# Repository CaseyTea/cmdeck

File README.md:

Watch the build video ↓

CM Deck is a clamshell style cyberdeck built around the Raspberry Pi Compute Module 5. It has a custom carrier board and a low profile mechanical keyboard.

<sub>⚠️ The PCBs will be updated to fix three issues: 1. The flash chip CS pin isn’t connected (see video at [11:09](https://youtu.be/U5GZeMm5nhI?si=vS6aNDHk9gTeop53&t=669)) | 2. Add jumper pads for the power button so I can solder wires and connect it to the power board (see video at [16:32](https://youtu.be/U5GZeMm5nhI?si=_Pz7x-TjfpxkA6fn&t=992)) | 3. Add an open jumper pad on the 3V3 line of the DSI connector on the main board (see video at [15:09](https://youtu.be/U5GZeMm5nhI?si=e3sX7tEprCDsY_S7&t=909))</sub>

[![CC BY-NC-SA 4.0][cc-by-nc-sa-shield]][cc-by-nc-sa]

[![CC BY-NC-SA 4.0][cc-by-nc-sa-image]][cc-by-nc-sa]

[cc-by-nc-sa]: http://creativecommons.org/licenses/by-nc-sa/4.0/
[cc-by-nc-sa-image]: https://licensebuttons.net/l/by-nc-sa/4.0/88x31.png
[cc-by-nc-sa-shield]: https://img.shields.io/badge/License-CC%20BY--NC--SA%204.0-lightgrey.svg

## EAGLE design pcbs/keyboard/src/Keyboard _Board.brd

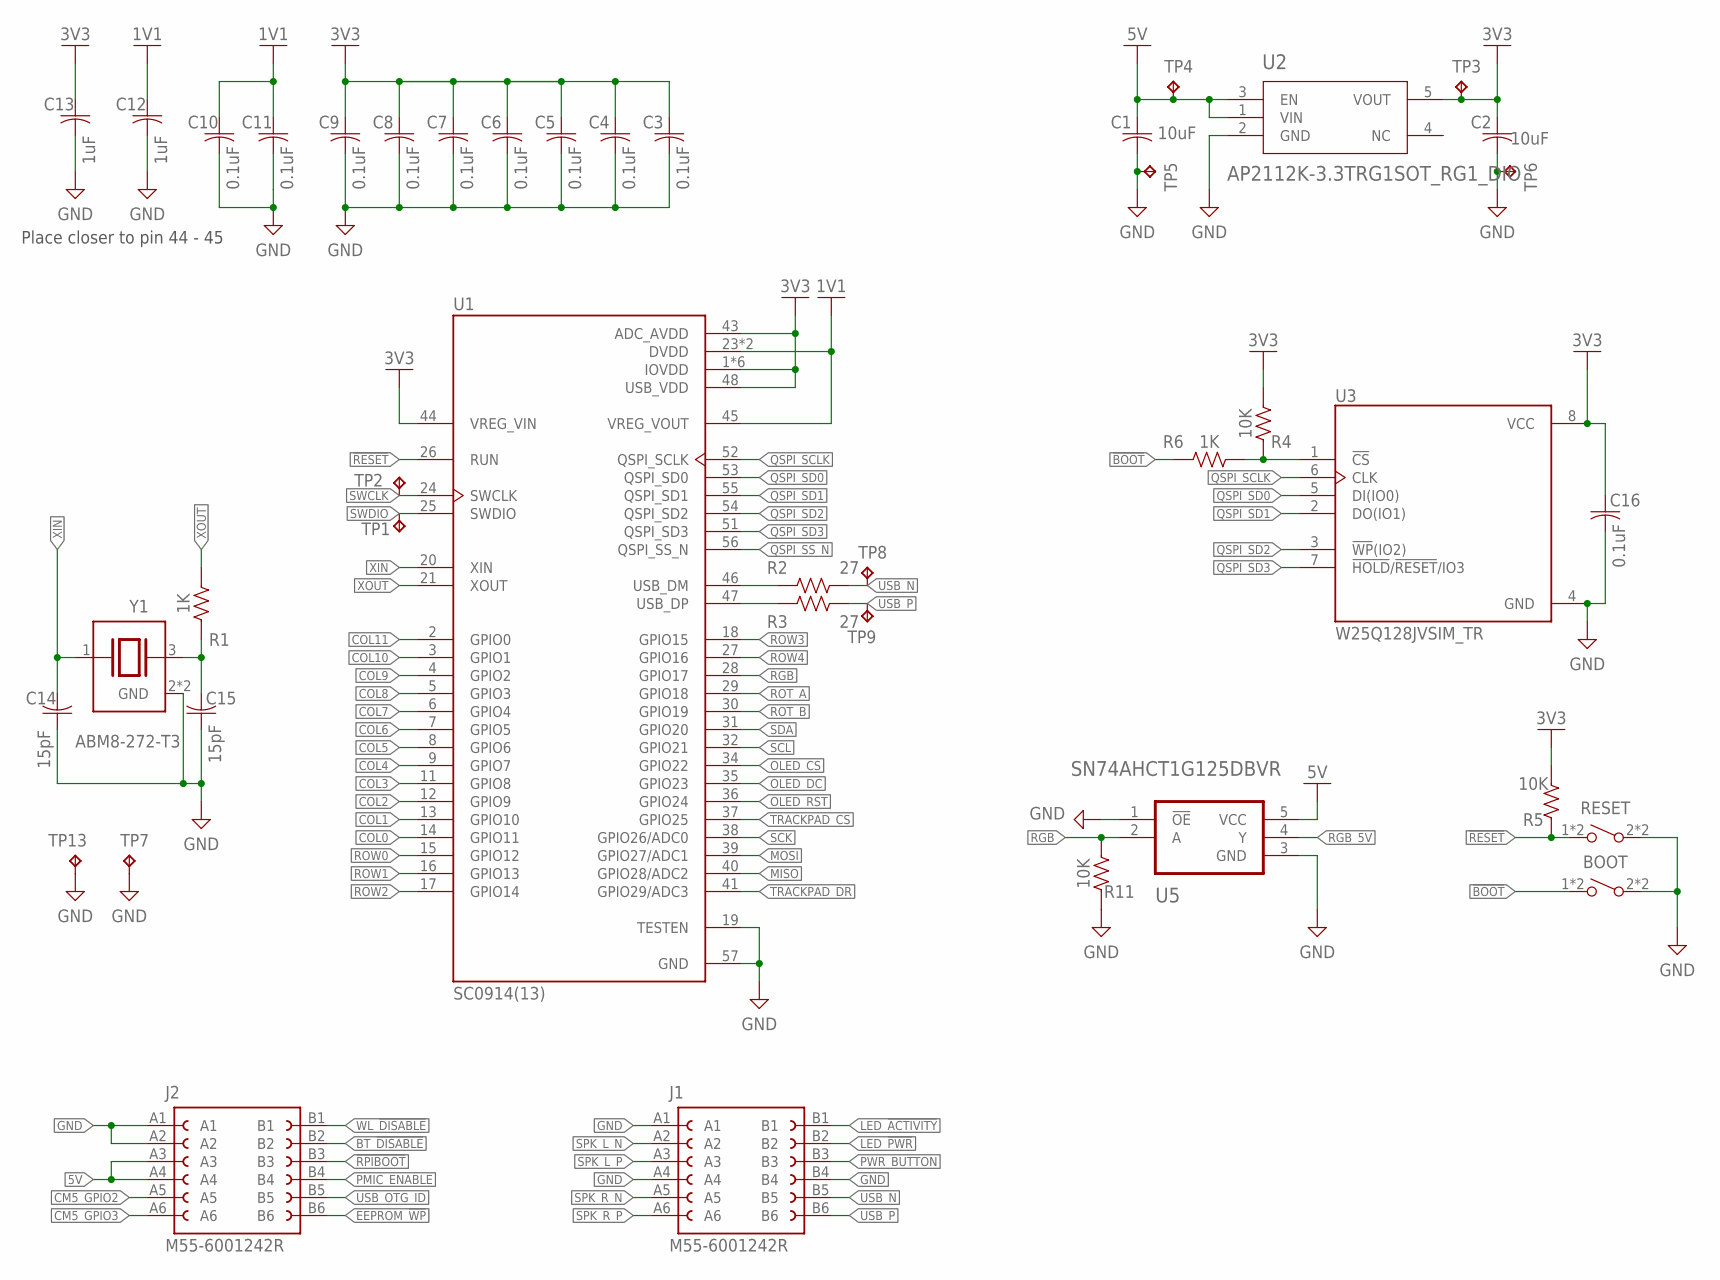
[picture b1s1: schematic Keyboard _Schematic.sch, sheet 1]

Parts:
BOOT: SPST-NO_SWITCH_KMR2; KMR2
C1, C2: 10uF; CAPC3216X135
C3, C4, C5, C6, C7, C8, C9, C10, C11, C16: 0.1uF; CAPC2012X110
C12, C13: 1uF; CAPC2012X110
C14, C15: 15pF; CAPC2012X110
J1, J2: M55-6001242R; HARWIN_M55-6001242R
R1, R6: 1K; RESC2012X65
R2, R3: 27; RESC2012X65
R4, R5, R11: 10K; RESC2012X65
RESET: SPST-NO_SWITCH_KMR2; KMR2
TP1, TP2, TP3, TP5, TP13: TPB2,54; B2,54
TP4, TP6, TP7, TP8, TP9: TPB1,27; B1,27
U1: SC0914(13); QFN40P700X700X90-57N
U2: AP2112K-3.3TRG1SOT_RG1_DIO; SOT_RG1_DIO
U3: W25Q128JVSIM_TR; SOIC127P790X216-8N
U5: SN74AHCT1G125DBVR; SOT95P280X145-5N
Y1: ABM8-272-T3; XTAL_ABM8-272-T3

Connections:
1V1: C10.1, C11.1, C12.1, U1.23 (DVDD), U1.45 (VREG_VOUT), U1.50 (DVDD)
3V3: C2.1, C3.1, C4.1, C5.1, C6.1, C7.1, C8.1, C9.1, C13.1, C16.1, R4.2, R5.2, TP3.TP, U1.1 (IOVDD), U1.10 (IOVDD), U1.22 (IOVDD), U1.33 (IOVDD), U1.42 (IOVDD), U1.43 (ADC_AVDD), U1.44 (VREG_VIN), U1.48 (USB_VDD), U1.49 (IOVDD), U2.5 (VOUT), U3.8 (VCC); also elsewhere on the board
5V: C1.1, J2.A3, J2.A4, TP4.TP, U2.1 (VIN), U2.3 (EN), U5.5 (VCC); also elsewhere on the board
!BOOT: BOOT.1, BOOT.4 (1), R6.1
!RESET: R5.1, RESET.1, RESET.4 (1), U1.26 (RUN)
!RPIBOOT: J2.B3; also elsewhere on the board
BT_!DISABLE: J2.B2; also elsewhere on the board
CM5_GPIO2: J2.A5; also elsewhere on the board
CM5_GPIO3: J2.A6; also elsewhere on the board
COL0: U1.14 (GPIO11); also elsewhere on the board
COL1: U1.13 (GPIO10); also elsewhere on the board
COL2: U1.12 (GPIO9); also elsewhere on the board
COL3: U1.11 (GPIO8); also elsewhere on the board
COL4: U1.9 (GPIO7); also elsewhere on the board
COL5: U1.8 (GPIO6); also elsewhere on the board
COL6: U1.7 (GPIO5); also elsewhere on the board
COL7: U1.6 (GPIO4); also elsewhere on the board
COL8: U1.5 (GPIO3); also elsewhere on the board
COL9: U1.4 (GPIO2); also elsewhere on the board
COL10: U1.3 (GPIO1); also elsewhere on the board
COL11: U1.2 (GPIO0); also elsewhere on the board
EEPROM_!WP: J2.B6; also elsewhere on the board
GND: BOOT.2, BOOT.3 (2), C1.2, C2.2, C3.2, C4.2, C5.2, C6.2, C7.2, C8.2, C9.2, C10.2, C11.2, C12.2, C13.2, C14.1, C15.1, C16.2, J1.A1, J1.A4, J1.B4, J2.A1, J2.A2, R11.1, RESET.2, RESET.3 (2), TP5.TP, TP6.TP, TP7.TP, TP13.TP, U1.19 (TESTEN), U1.57 (GND), U2.2 (GND), U3.4 (GND), U5.1 (!OE), U5.3 (GND), Y1.2 (GND), Y1.4 (GND); also elsewhere on the board
LED_!ACTIVITY: J1.B1; also elsewhere on the board
LED_!PWR: J1.B2; also elsewhere on the board
MISO: U1.40 (GPIO28/ADC2); also elsewhere on the board
MOSI: U1.39 (GPIO27/ADC1); also elsewhere on the board
unnamed: C15.2, R1.1, Y1.3
OLED_CS: U1.34 (GPIO22); also elsewhere on the board
OLED_DC: U1.35 (GPIO23); also elsewhere on the board
OLED_RST: U1.36 (GPIO24); also elsewhere on the board
PMIC_ENABLE: J2.B4; also elsewhere on the board
PWR_BUTTON: J1.B3; also elsewhere on the board
QSPI_SCLK: U1.52 (QSPI_SCLK), U3.6 (CLK)
QSPI_SD0: U1.53 (QSPI_SD0), U3.5 (DI(IO0))
QSPI_SD1: U1.55 (QSPI_SD1), U3.2 (DO(IO1))
QSPI_SD2: U1.54 (QSPI_SD2), U3.3 (!WP!(IO2))
QSPI_SD3: U1.51 (QSPI_SD3), U3.7 (!HOLD!/!RESET!/IO3)
QSPI_SS_N: R4.1, R6.2, U1.56 (QSPI_SS_N), U3.1 (!CS)
RGB: R11.2, U1.28 (GPIO17), U5.2 (A)
RGB_5V: U5.4 (Y); also elsewhere on the board
ROT_A: U1.29 (GPIO18); also elsewhere on the board
ROT_B: U1.30 (GPIO19); also elsewhere on the board
ROW0: U1.15 (GPIO12); also elsewhere on the board
ROW1: U1.16 (GPIO13); also elsewhere on the board
ROW2: U1.17 (GPIO14); also elsewhere on the board
ROW3: U1.18 (GPIO15); also elsewhere on the board
ROW4: U1.27 (GPIO16); also elsewhere on the board
SCK: U1.38 (GPIO26/ADC0); also elsewhere on the board
SCL: U1.32 (GPIO21); also elsewhere on the board
SDA: U1.31 (GPIO20); also elsewhere on the board
SPK_L_N: J1.A2; also elsewhere on the board
SPK_L_P: J1.A3; also elsewhere on the board
SPK_R_N: J1.A5; also elsewhere on the board
SPK_R_P: J1.A6; also elsewhere on the board
SWCLK: TP2.TP, U1.24 (SWCLK)
SWDIO: TP1.TP, U1.25 (SWDIO)
TRACKPAD_CS: U1.37 (GPIO25); also elsewhere on the board
TRACKPAD_DR: U1.41 (GPIO29/ADC3); also elsewhere on the board
USB_D_N: R2.1, U1.46 (USB_DM)
USB_D_P: R3.2, U1.47 (USB_DP)
USB_N: J1.B5, R2.2, TP8.TP
USB_OTG_ID: J2.B5; also elsewhere on the board
USB_P: J1.B6, R3.1, TP9.TP
WL_!DISABLE: J2.B1; also elsewhere on the board
XIN: C14.2, U1.20 (XIN), Y1.1
XOUT: R1.2, U1.21 (XOUT)

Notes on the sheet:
Place closer to pin 44 - 45

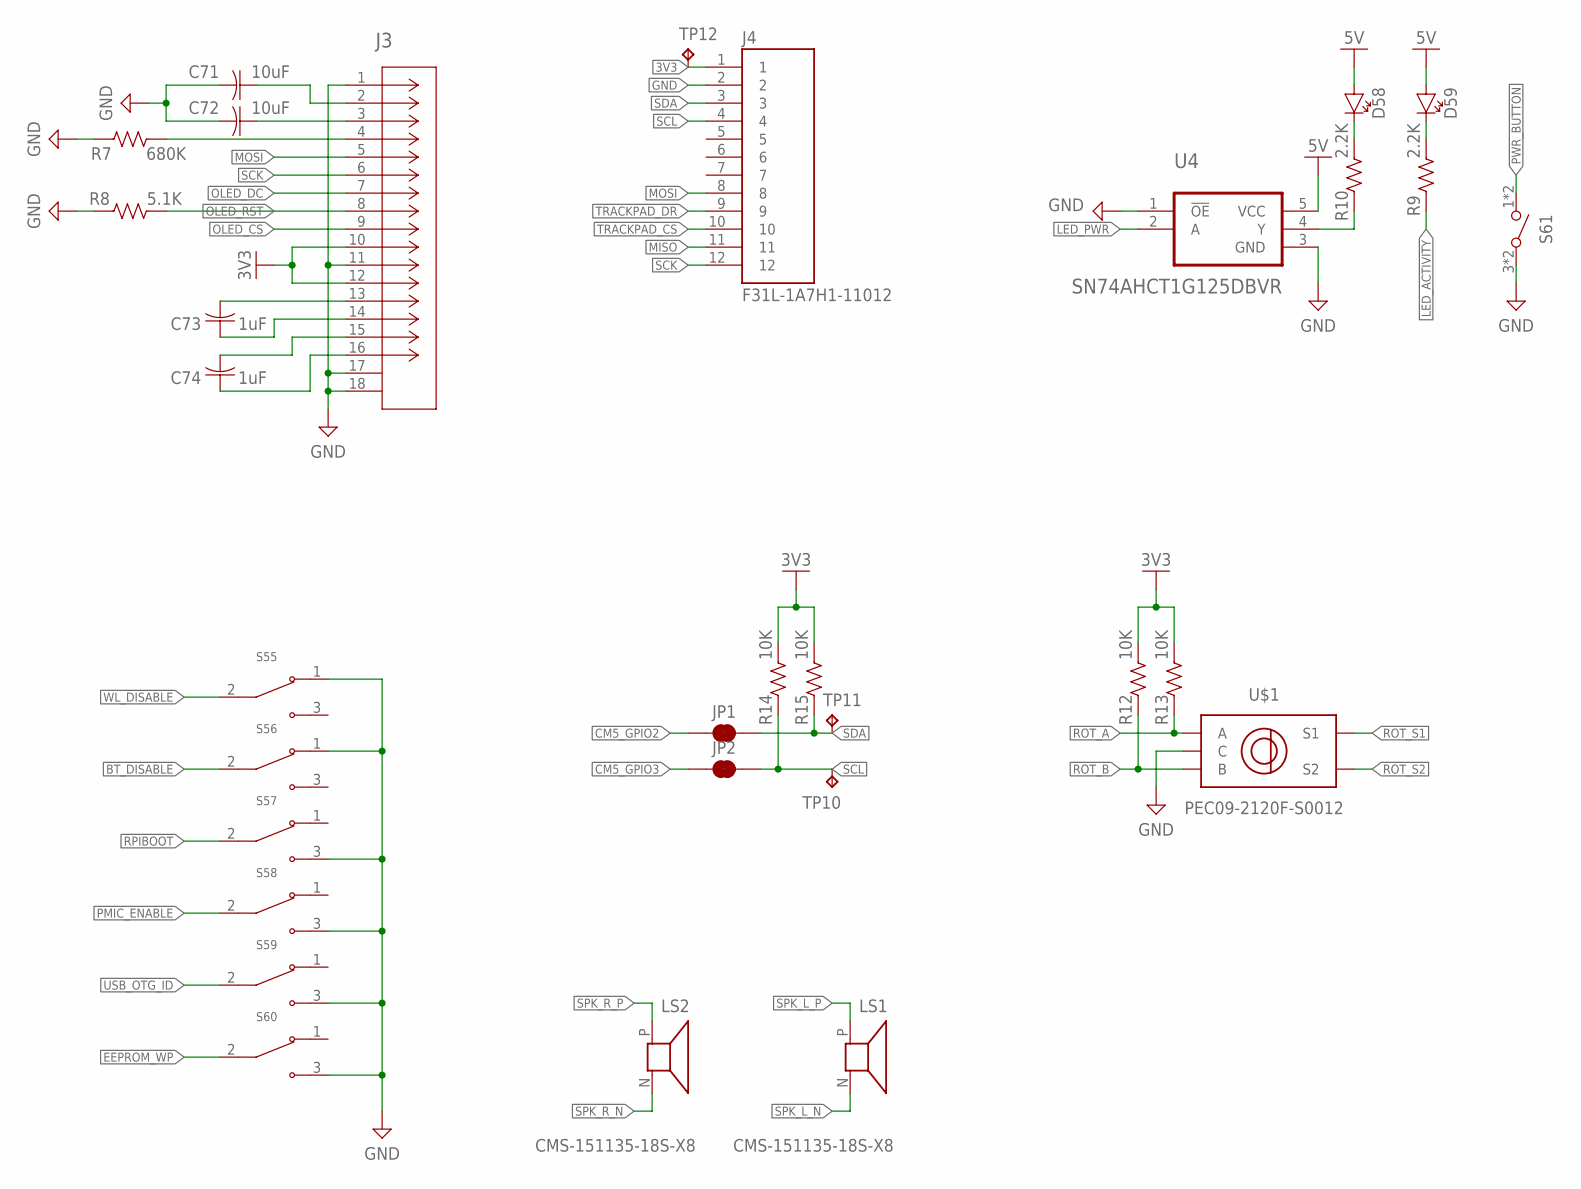
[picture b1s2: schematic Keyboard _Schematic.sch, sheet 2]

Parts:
C71, C72: 10uF; CAPC3216X135
C73, C74: 1uF; CAPC2012X110
D58, D59: CHIP-FLAT-G_1206; LEDC3216X75N_FLAT-G
J3: 1-1775333-6CONN16_1-1775333-6_TEC; CONN16_1-1775333-6_TEC
J4: F31L-1A7H1-11012; AMPHENOL_F31L-1A7H1-11012
JP1, JP2: JUMPER-SMT_2_NC_TRACE_NO-SILK; SMT-JUMPER_2_NC_TRACE_NO-SILK
LS1, LS2: CMS-151135-18S-X8; SPKR_CMS-151135-18S-X8
R7: 680K; RESC2012X65
R8: 5.1K; RESC2012X65
R9, R10: 2.2K; RESC2012X65
R12, R13, R14, R15: 10K; RESC2012X65
S55, S56, S57, S58, S59, S60: SLW-1277744-3A-N-D; SW_SLW-1277744-3A-N-D
S61: SPST-NO_SWITCH_PTS645-SMT-6MM; PTS645-SMT-6MM
TP10, TP11, TP12: TPB1,27; B1,27
U4: SN74AHCT1G125DBVR; SOT95P280X145-5N
U$1: PEC09-2120F-S0012; PEC09-2XXXF-SXXXX

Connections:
3V3: J3.10, J3.12, J4.1, R12.2, R13.2, R14.2, R15.2, TP12.TP; also elsewhere on the board
5V: D58.A, D59.A, U4.5 (VCC); also elsewhere on the board
!RPIBOOT: S57.2; also elsewhere on the board
BT_!DISABLE: S56.2; also elsewhere on the board
CM5_GPIO2: JP1.1; also elsewhere on the board
CM5_GPIO3: JP2.1; also elsewhere on the board
EEPROM_!WP: S60.2; also elsewhere on the board
GND: C71.2, C72.2, J3.1, J3.11, J3.17, J3.18, J4.2, R7.1, R8.1, S55.1, S56.1, S57.3, S58.3, S59.3, S60.3, S61.3 (2), S61.4 (2), U4.1 (!OE), U4.3 (GND), U$1.P$2 (C); also elsewhere on the board
LED_!ACTIVITY: R9.1; also elsewhere on the board
LED_!PWR: U4.2 (A); also elsewhere on the board
MISO: J4.11; also elsewhere on the board
MOSI: J3.5, J4.8; also elsewhere on the board
unnamed: D59.C, R9.2
unnamed: C71.1, J3.2
unnamed: C72.1, J3.3
unnamed: J3.4, R7.2
unnamed: C73.2, J3.13
unnamed: C73.1, J3.14
unnamed: C74.2, J3.15
unnamed: C74.1, J3.16
unnamed: D58.C, R10.2
unnamed: R10.1, U4.4 (Y)
OLED_CS: J3.9; also elsewhere on the board
OLED_DC: J3.7; also elsewhere on the board
OLED_RST: J3.8, R8.2; also elsewhere on the board
PMIC_ENABLE: S58.2; also elsewhere on the board
PWR_BUTTON: S61.1, S61.2 (1); also elsewhere on the board
ROT_A: R13.1, U$1.P$3 (A); also elsewhere on the board
ROT_B: R12.1, U$1.P$1 (B); also elsewhere on the board
ROT_S1: U$1.P$4 (S1); also elsewhere on the board
ROT_S2: U$1.P$5 (S2); also elsewhere on the board
SCK: J3.6, J4.12; also elsewhere on the board
SCL: J4.4, JP2.2, R14.1, TP10.TP; also elsewhere on the board
SDA: J4.3, JP1.2, R15.1, TP11.TP; also elsewhere on the board
SPK_L_N: LS1.N; also elsewhere on the board
SPK_L_P: LS1.P; also elsewhere on the board
SPK_R_N: LS2.N; also elsewhere on the board
SPK_R_P: LS2.P; also elsewhere on the board
TRACKPAD_CS: J4.10; also elsewhere on the board
TRACKPAD_DR: J4.9; also elsewhere on the board
USB_OTG_ID: S59.2; also elsewhere on the board
WL_!DISABLE: S55.2; also elsewhere on the board

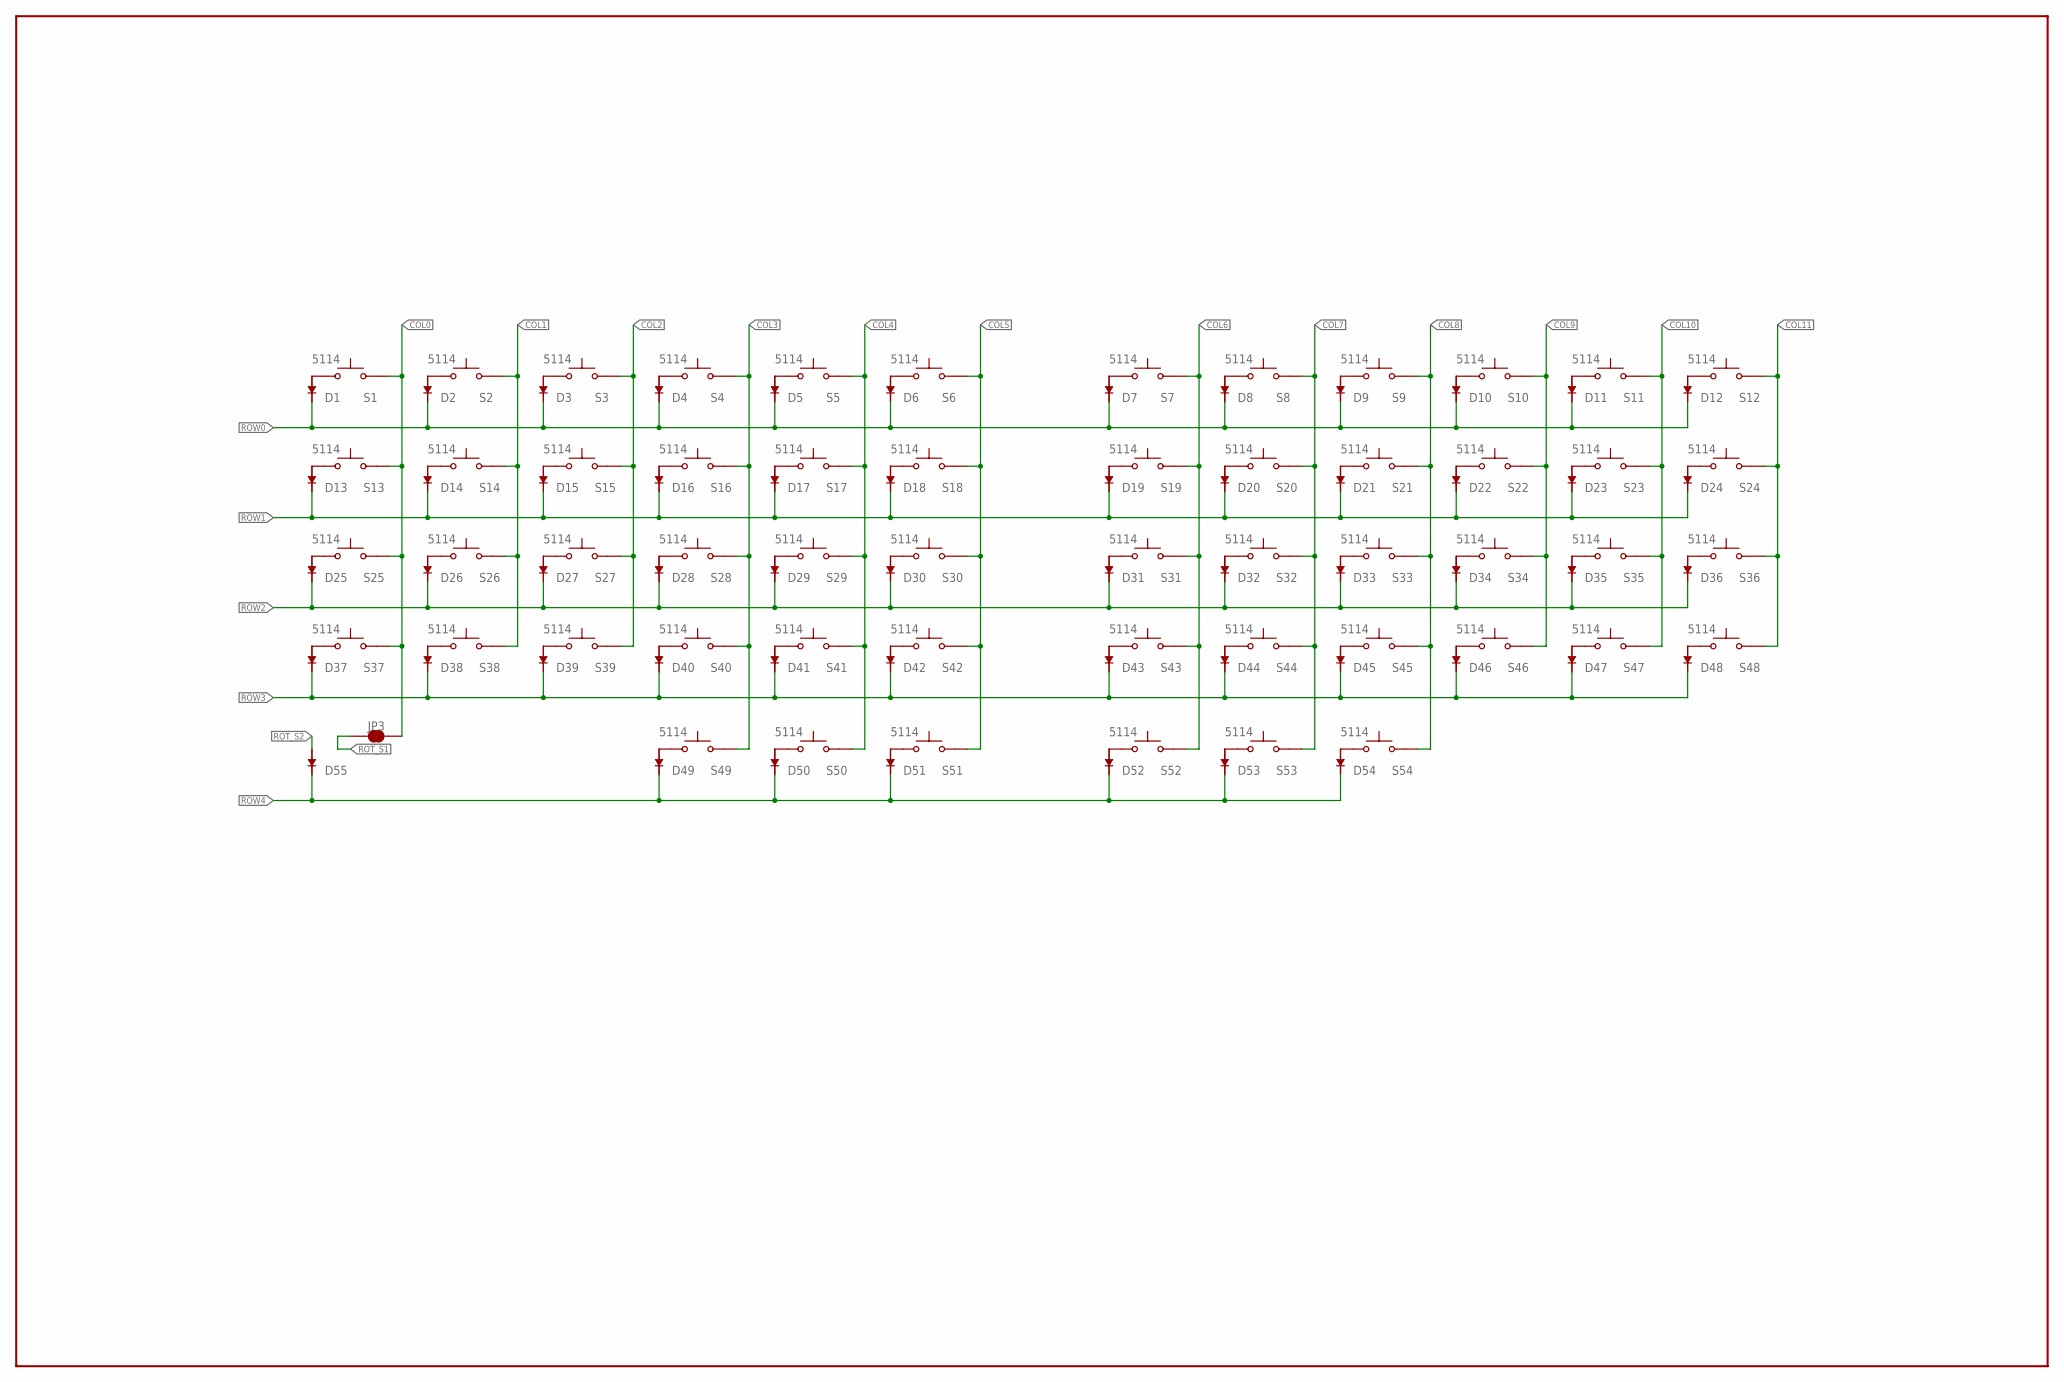
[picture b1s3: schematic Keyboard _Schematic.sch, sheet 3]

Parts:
D1, D2, D3, D4, D5, D6, D7, D8, D9, D10, D11, D12, D13, D14, D15, D16, D17, D18, D19, D20, D21, D22, D23, D24, D25, D26, D27, D28, D29, D30, D31, D32, D33, D34, D35, D36, D37, D38, D39, D40, D41, D42, D43, D44, D45, D46, D47, D48, D49, D50, D51, D52, D53, D54, D55: 1N4148W; SOD3715X135N
JP3: JUMPER-SMT_2_NC_TRACE_NO-SILK; SMT-JUMPER_2_NC_TRACE_NO-SILK
S1, S2, S3, S4, S5, S6, S7, S8, S9, S10, S11, S12, S13, S14, S15, S16, S17, S18, S19, S20, S21, S22, S23, S24, S25, S26, S27, S28, S29, S30, S31, S32, S33, S34, S35, S36, S37, S38, S39, S40, S41, S42, S43, S44, S45, S46, S47, S48, S49, S50, S51, S52, S53, S54: 5114; SW_5114

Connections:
COL0: JP3.1, S1.P$2 (2), S13.P$2 (2), S25.P$2 (2), S37.P$2 (2); also elsewhere on the board
COL1: S2.P$2 (2), S14.P$2 (2), S26.P$2 (2), S38.P$2 (2); also elsewhere on the board
COL2: S3.P$2 (2), S15.P$2 (2), S27.P$2 (2), S39.P$2 (2); also elsewhere on the board
COL3: S4.P$2 (2), S16.P$2 (2), S28.P$2 (2), S40.P$2 (2), S49.P$2 (2); also elsewhere on the board
COL4: S5.P$2 (2), S17.P$2 (2), S29.P$2 (2), S41.P$2 (2), S50.P$2 (2); also elsewhere on the board
COL5: S6.P$2 (2), S18.P$2 (2), S30.P$2 (2), S42.P$2 (2), S51.P$2 (2); also elsewhere on the board
COL6: S7.P$2 (2), S19.P$2 (2), S31.P$2 (2), S43.P$2 (2), S52.P$2 (2); also elsewhere on the board
COL7: S8.P$2 (2), S20.P$2 (2), S32.P$2 (2), S44.P$2 (2), S53.P$2 (2); also elsewhere on the board
COL8: S9.P$2 (2), S21.P$2 (2), S33.P$2 (2), S45.P$2 (2), S54.P$2 (2); also elsewhere on the board
COL9: S10.P$2 (2), S22.P$2 (2), S34.P$2 (2), S46.P$2 (2); also elsewhere on the board
COL10: S11.P$2 (2), S23.P$2 (2), S35.P$2 (2), S47.P$2 (2); also elsewhere on the board
COL11: S12.P$2 (2), S24.P$2 (2), S36.P$2 (2), S48.P$2 (2); also elsewhere on the board
unnamed: D1.A, S1.P$1 (1)
unnamed: D2.A, S2.P$1 (1)
unnamed: D3.A, S3.P$1 (1)
unnamed: D4.A, S4.P$1 (1)
unnamed: D5.A, S5.P$1 (1)
unnamed: D6.A, S6.P$1 (1)
unnamed: D7.A, S7.P$1 (1)
unnamed: D8.A, S8.P$1 (1)
unnamed: D9.A, S9.P$1 (1)
unnamed: D10.A, S10.P$1 (1)
unnamed: D11.A, S11.P$1 (1)
unnamed: D12.A, S12.P$1 (1)
unnamed: D13.A, S13.P$1 (1)
unnamed: D14.A, S14.P$1 (1)
unnamed: D15.A, S15.P$1 (1)
unnamed: D16.A, S16.P$1 (1)
unnamed: D17.A, S17.P$1 (1)
unnamed: D18.A, S18.P$1 (1)
unnamed: D19.A, S19.P$1 (1)
unnamed: D20.A, S20.P$1 (1)
unnamed: D21.A, S21.P$1 (1)
unnamed: D22.A, S22.P$1 (1)
unnamed: D23.A, S23.P$1 (1)
unnamed: D24.A, S24.P$1 (1)
unnamed: D25.A, S25.P$1 (1)
unnamed: D26.A, S26.P$1 (1)
unnamed: D27.A, S27.P$1 (1)
unnamed: D28.A, S28.P$1 (1)
unnamed: D29.A, S29.P$1 (1)
unnamed: D30.A, S30.P$1 (1)
unnamed: D31.A, S31.P$1 (1)
unnamed: D32.A, S32.P$1 (1)
unnamed: D33.A, S33.P$1 (1)
unnamed: D34.A, S34.P$1 (1)
unnamed: D35.A, S35.P$1 (1)
unnamed: D36.A, S36.P$1 (1)
unnamed: D37.A, S37.P$1 (1)
unnamed: D38.A, S38.P$1 (1)
unnamed: D39.A, S39.P$1 (1)
unnamed: D40.A, S40.P$1 (1)
unnamed: D41.A, S41.P$1 (1)
unnamed: D42.A, S42.P$1 (1)
unnamed: D43.A, S43.P$1 (1)
unnamed: D44.A, S44.P$1 (1)
unnamed: D45.A, S45.P$1 (1)
unnamed: D46.A, S46.P$1 (1)
unnamed: D47.A, S47.P$1 (1)
unnamed: D48.A, S48.P$1 (1)
unnamed: D49.A, S49.P$1 (1)
unnamed: D50.A, S50.P$1 (1)
unnamed: D51.A, S51.P$1 (1)
unnamed: D52.A, S52.P$1 (1)
unnamed: D53.A, S53.P$1 (1)
unnamed: D54.A, S54.P$1 (1)
ROT_S1: JP3.2; also elsewhere on the board
ROT_S2: D55.A; also elsewhere on the board
ROW0: D1.C (K), D2.C (K), D3.C (K), D4.C (K), D5.C (K), D6.C (K), D7.C (K), D8.C (K), D9.C (K), D10.C (K), D11.C (K), D12.C (K); also elsewhere on the board
ROW1: D13.C (K), D14.C (K), D15.C (K), D16.C (K), D17.C (K), D18.C (K), D19.C (K), D20.C (K), D21.C (K), D22.C (K), D23.C (K), D24.C (K); also elsewhere on the board
ROW2: D25.C (K), D26.C (K), D27.C (K), D28.C (K), D29.C (K), D30.C (K), D31.C (K), D32.C (K), D33.C (K), D34.C (K), D35.C (K), D36.C (K); also elsewhere on the board
ROW3: D37.C (K), D38.C (K), D39.C (K), D40.C (K), D41.C (K), D42.C (K), D43.C (K), D44.C (K), D45.C (K), D46.C (K), D47.C (K), D48.C (K); also elsewhere on the board
ROW4: D49.C (K), D50.C (K), D51.C (K), D52.C (K), D53.C (K), D54.C (K), D55.C (K); also elsewhere on the board

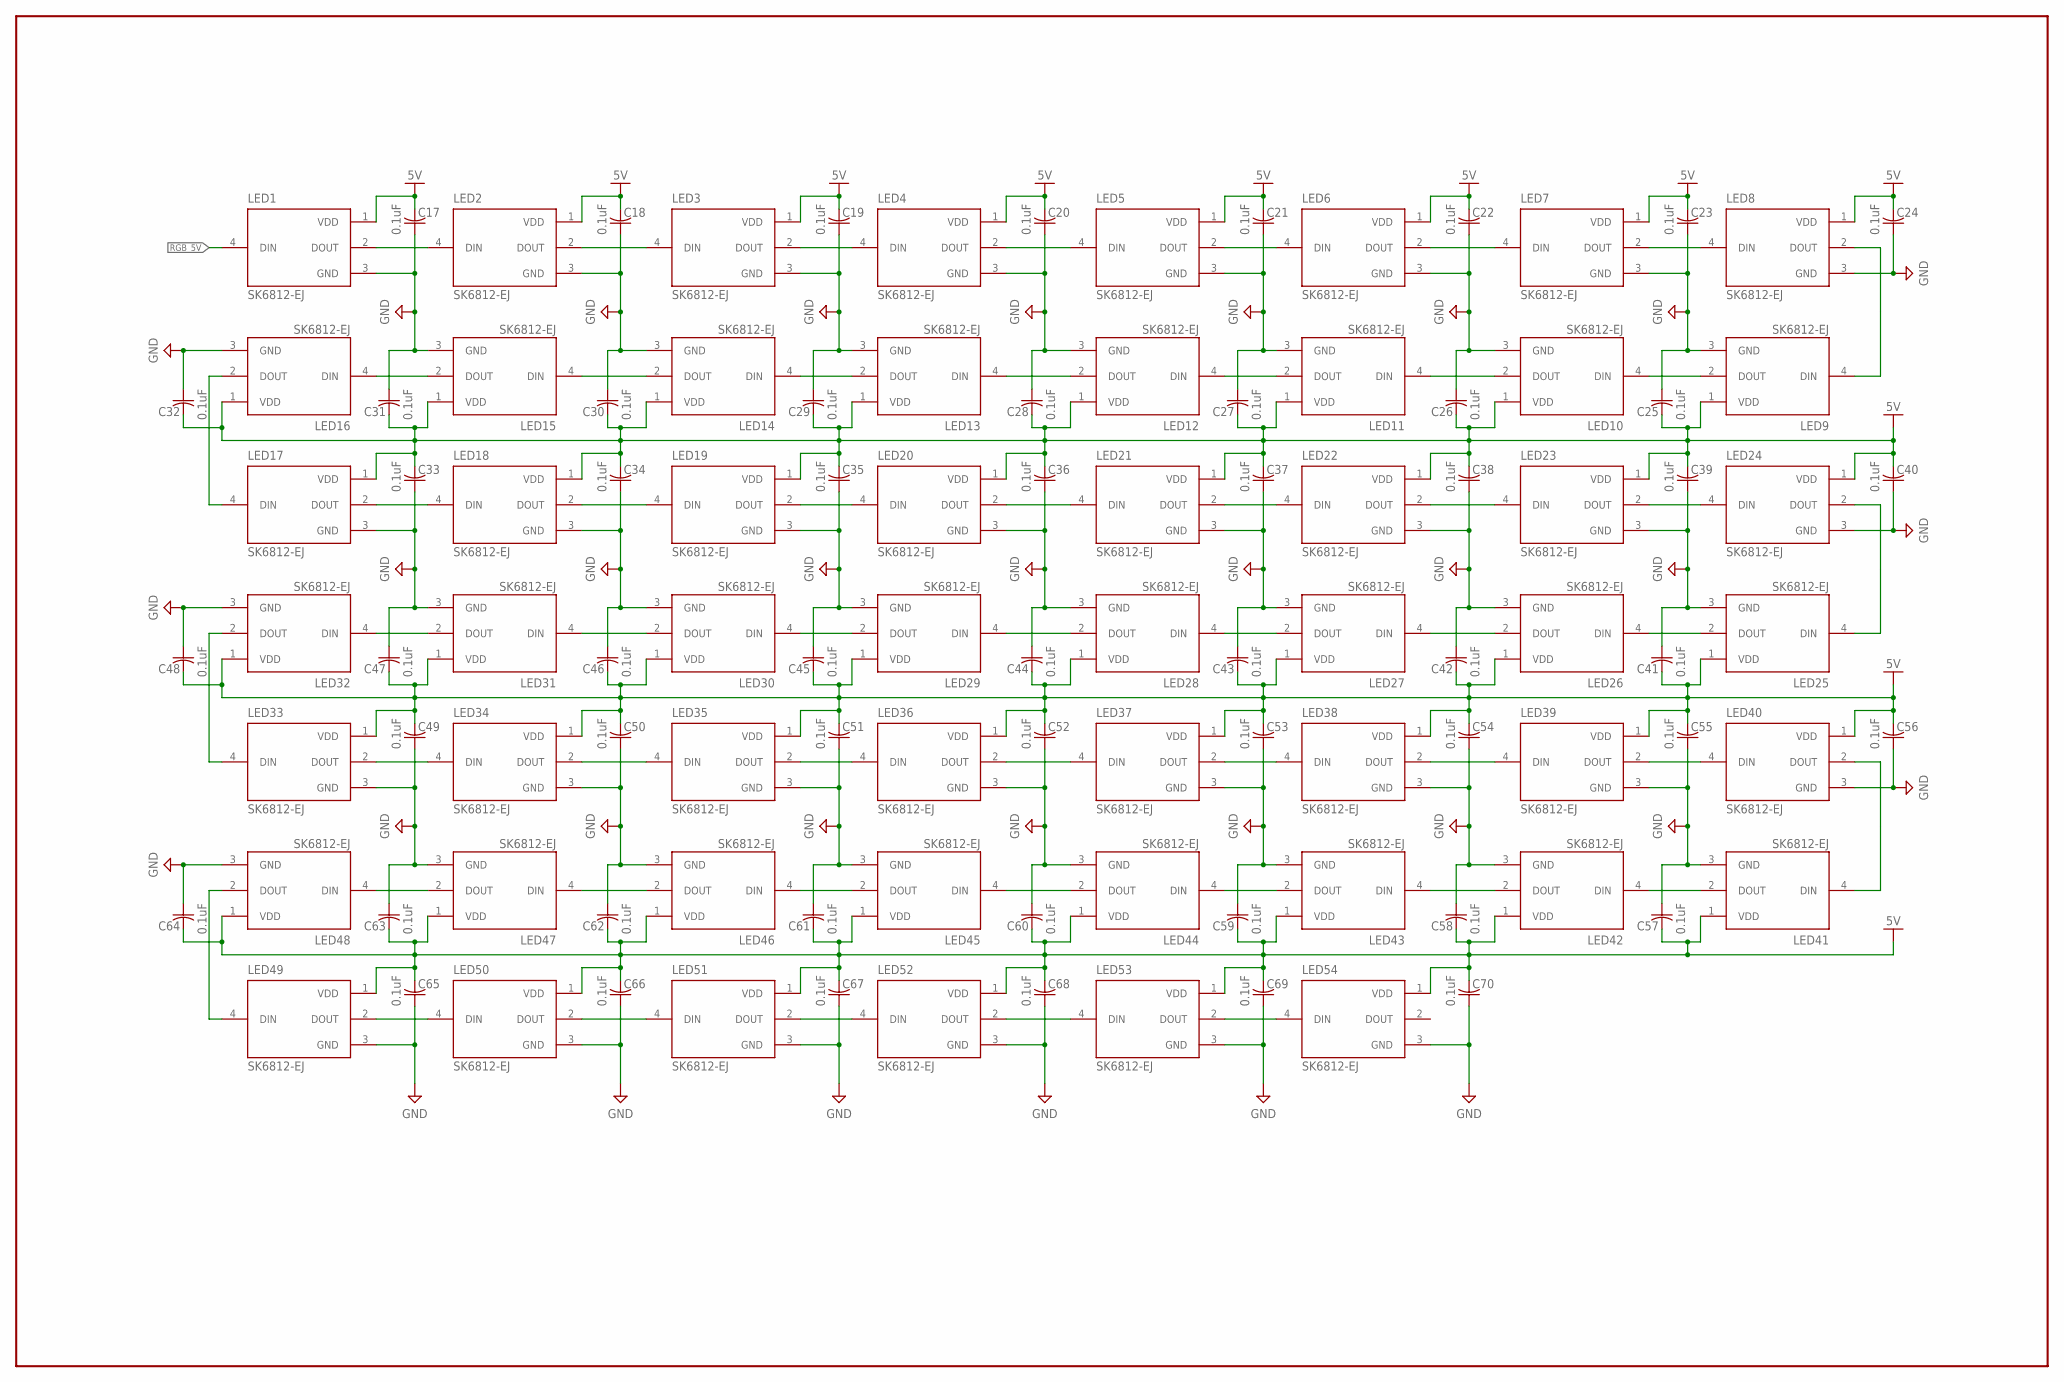
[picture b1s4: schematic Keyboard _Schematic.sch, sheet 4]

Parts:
C17, C18, C19, C20, C21, C22, C23, C24, C25, C26, C27, C28, C29, C30, C31, C32, C33, C34, C35, C36, C37, C38, C39, C40, C41, C42, C43, C44, C45, C46, C47, C48, C49, C50, C51, C52, C53, C54, C55, C56, C57, C58, C59, C60, C61, C62, C63, C64, C65, C66, C67, C68, C69, C70: 0.1uF; CAPC2012X110
LED1, LED2, LED3, LED4, LED5, LED6, LED7, LED8, LED9, LED10, LED11, LED12, LED13, LED14, LED15, LED16, LED17, LED18, LED19, LED20, LED21, LED22, LED23, LED24, LED25, LED26, LED27, LED28, LED29, LED30, LED31, LED32, LED33, LED34, LED35, LED36, LED37, LED38, LED39, LED40, LED41, LED42, LED43, LED44, LED45, LED46, LED47, LED48, LED49, LED50, LED51, LED52, LED53, LED54: SK6812-EJ; LED_SK6812-E

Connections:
5V: C17.2, C18.2, C19.2, C20.2, C21.2, C22.2, C23.2, C24.2, C25.2, C26.2, C27.2, C28.2, C29.2, C30.2, C31.2, C32.2, C33.2, C34.2, C35.2, C36.2, C37.2, C38.2, C39.2, C40.2, C41.2, C42.2, C43.2, C44.2, C45.2, C46.2, C47.2, C48.2, C49.2, C50.2, C51.2, C52.2, C53.2, C54.2, C55.2, C56.2, C57.2, C58.2, C59.2, C60.2, C61.2, C62.2, C63.2, C64.2, C65.2, C66.2, C67.2, C68.2, C69.2, C70.2, LED1.1 (VDD), LED2.1 (VDD), LED3.1 (VDD), LED4.1 (VDD), LED5.1 (VDD), LED6.1 (VDD), LED7.1 (VDD), LED8.1 (VDD), LED9.1 (VDD), LED10.1 (VDD), LED11.1 (VDD), LED12.1 (VDD), LED13.1 (VDD), LED14.1 (VDD), LED15.1 (VDD), LED16.1 (VDD), LED17.1 (VDD), LED18.1 (VDD), LED19.1 (VDD), LED20.1 (VDD), LED21.1 (VDD), LED22.1 (VDD), LED23.1 (VDD), LED24.1 (VDD), LED25.1 (VDD), LED26.1 (VDD), LED27.1 (VDD), LED28.1 (VDD), LED29.1 (VDD), LED30.1 (VDD), LED31.1 (VDD), LED32.1 (VDD), LED33.1 (VDD), LED34.1 (VDD), LED35.1 (VDD), LED36.1 (VDD), LED37.1 (VDD), LED38.1 (VDD), LED39.1 (VDD), LED40.1 (VDD), LED41.1 (VDD), LED42.1 (VDD), LED43.1 (VDD), LED44.1 (VDD), LED45.1 (VDD), LED46.1 (VDD), LED47.1 (VDD), LED48.1 (VDD), LED49.1 (VDD), LED50.1 (VDD), LED51.1 (VDD), LED52.1 (VDD), LED53.1 (VDD), LED54.1 (VDD); also elsewhere on the board
GND: C17.1, C18.1, C19.1, C20.1, C21.1, C22.1, C23.1, C24.1, C25.1, C26.1, C27.1, C28.1, C29.1, C30.1, C31.1, C32.1, C33.1, C34.1, C35.1, C36.1, C37.1, C38.1, C39.1, C40.1, C41.1, C42.1, C43.1, C44.1, C45.1, C46.1, C47.1, C48.1, C49.1, C50.1, C51.1, C52.1, C53.1, C54.1, C55.1, C56.1, C57.1, C58.1, C59.1, C60.1, C61.1, C62.1, C63.1, C64.1, C65.1, C66.1, C67.1, C68.1, C69.1, C70.1, LED1.3 (GND), LED2.3 (GND), LED3.3 (GND), LED4.3 (GND), LED5.3 (GND), LED6.3 (GND), LED7.3 (GND), LED8.3 (GND), LED9.3 (GND), LED10.3 (GND), LED11.3 (GND), LED12.3 (GND), LED13.3 (GND), LED14.3 (GND), LED15.3 (GND), LED16.3 (GND), LED17.3 (GND), LED18.3 (GND), LED19.3 (GND), LED20.3 (GND), LED21.3 (GND), LED22.3 (GND), LED23.3 (GND), LED24.3 (GND), LED25.3 (GND), LED26.3 (GND), LED27.3 (GND), LED28.3 (GND), LED29.3 (GND), LED30.3 (GND), LED31.3 (GND), LED32.3 (GND), LED33.3 (GND), LED34.3 (GND), LED35.3 (GND), LED36.3 (GND), LED37.3 (GND), LED38.3 (GND), LED39.3 (GND), LED40.3 (GND), LED41.3 (GND), LED42.3 (GND), LED43.3 (GND), LED44.3 (GND), LED45.3 (GND), LED46.3 (GND), LED47.3 (GND), LED48.3 (GND), LED49.3 (GND), LED50.3 (GND), LED51.3 (GND), LED52.3 (GND), LED53.3 (GND), LED54.3 (GND); also elsewhere on the board
unnamed: LED8.2 (DOUT), LED9.4 (DIN)
unnamed: LED24.2 (DOUT), LED25.4 (DIN)
unnamed: LED1.2 (DOUT), LED2.4 (DIN)
unnamed: LED17.2 (DOUT), LED18.4 (DIN)
unnamed: LED3.2 (DOUT), LED4.4 (DIN)
unnamed: LED2.2 (DOUT), LED3.4 (DIN)
unnamed: LED5.2 (DOUT), LED6.4 (DIN)
unnamed: LED19.2 (DOUT), LED20.4 (DIN)
unnamed: LED40.2 (DOUT), LED41.4 (DIN)
unnamed: LED18.2 (DOUT), LED19.4 (DIN)
unnamed: LED7.2 (DOUT), LED8.4 (DIN)
unnamed: LED6.2 (DOUT), LED7.4 (DIN)
unnamed: LED4.2 (DOUT), LED5.4 (DIN)
unnamed: LED9.2 (DOUT), LED10.4 (DIN)
unnamed: LED21.2 (DOUT), LED22.4 (DIN)
unnamed: LED11.2 (DOUT), LED12.4 (DIN)
unnamed: LED10.2 (DOUT), LED11.4 (DIN)
unnamed: LED13.2 (DOUT), LED14.4 (DIN)
unnamed: LED23.2 (DOUT), LED24.4 (DIN)
unnamed: LED22.2 (DOUT), LED23.4 (DIN)
unnamed: LED15.2 (DOUT), LED16.4 (DIN)
unnamed: LED14.2 (DOUT), LED15.4 (DIN)
unnamed: LED12.2 (DOUT), LED13.4 (DIN)
unnamed: LED20.2 (DOUT), LED21.4 (DIN)
unnamed: LED25.2 (DOUT), LED26.4 (DIN)
unnamed: LED27.2 (DOUT), LED28.4 (DIN)
unnamed: LED26.2 (DOUT), LED27.4 (DIN)
unnamed: LED29.2 (DOUT), LED30.4 (DIN)
unnamed: LED31.2 (DOUT), LED32.4 (DIN)
unnamed: LED30.2 (DOUT), LED31.4 (DIN)
unnamed: LED28.2 (DOUT), LED29.4 (DIN)
unnamed: LED16.2 (DOUT), LED17.4 (DIN)
unnamed: LED33.2 (DOUT), LED34.4 (DIN)
unnamed: LED35.2 (DOUT), LED36.4 (DIN)
unnamed: LED34.2 (DOUT), LED35.4 (DIN)
unnamed: LED37.2 (DOUT), LED38.4 (DIN)
unnamed: LED39.2 (DOUT), LED40.4 (DIN)
unnamed: LED38.2 (DOUT), LED39.4 (DIN)
unnamed: LED36.2 (DOUT), LED37.4 (DIN)
unnamed: LED41.2 (DOUT), LED42.4 (DIN)
unnamed: LED43.2 (DOUT), LED44.4 (DIN)
unnamed: LED42.2 (DOUT), LED43.4 (DIN)
unnamed: LED45.2 (DOUT), LED46.4 (DIN)
unnamed: LED47.2 (DOUT), LED48.4 (DIN)
unnamed: LED46.2 (DOUT), LED47.4 (DIN)
unnamed: LED44.2 (DOUT), LED45.4 (DIN)
unnamed: LED32.2 (DOUT), LED33.4 (DIN)
unnamed: LED49.2 (DOUT), LED50.4 (DIN)
unnamed: LED51.2 (DOUT), LED52.4 (DIN)
unnamed: LED50.2 (DOUT), LED51.4 (DIN)
unnamed: LED53.2 (DOUT), LED54.4 (DIN)
unnamed: LED48.2 (DOUT), LED49.4 (DIN)
unnamed: LED52.2 (DOUT), LED53.4 (DIN)
RGB_5V: LED1.4 (DIN); also elsewhere on the board

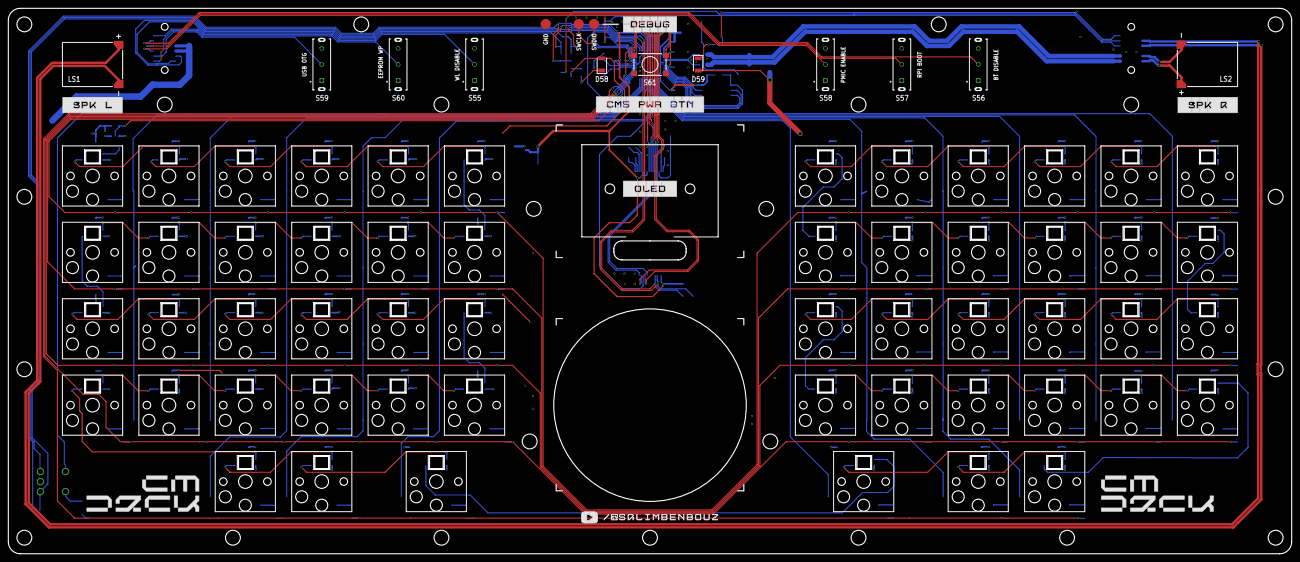
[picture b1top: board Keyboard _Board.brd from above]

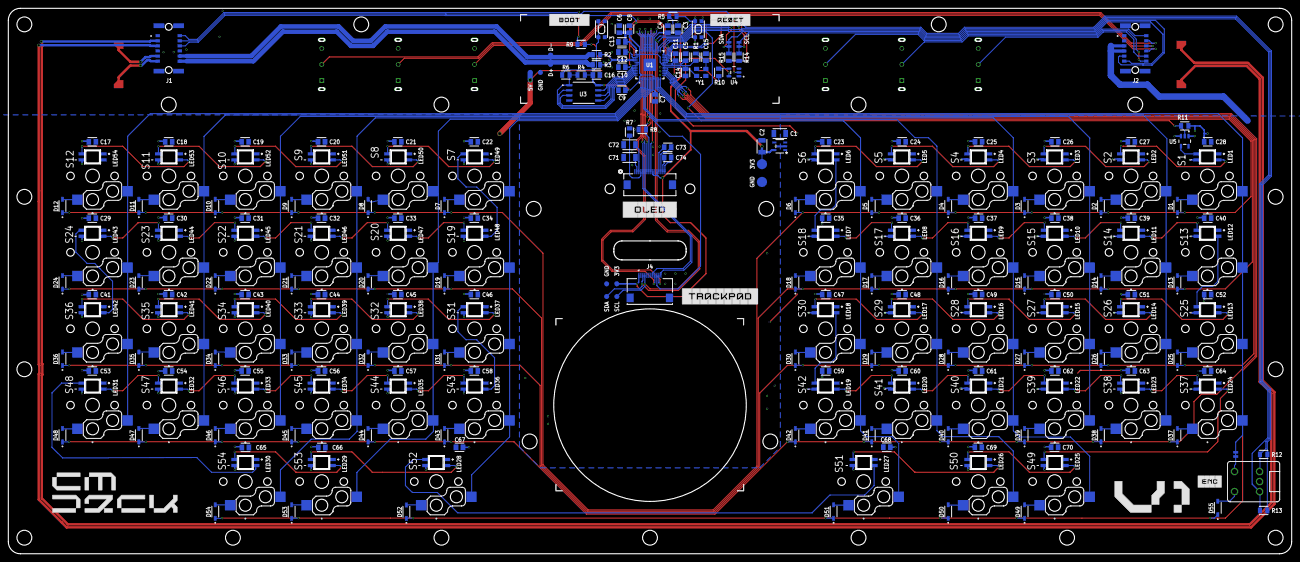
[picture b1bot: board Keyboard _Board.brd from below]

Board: 2 copper layers, 320.0 x 136.0 mm, 292 parts (278 on the bottom side), 186 nets.

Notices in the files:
parts and their libraries:
SparkFun-Jumpers: Licensing: Creative Commons ShareAlike 4.0 International - https://creativecommons.org/licenses/by-sa/4.0
COPYRIGHT: Copyright (C) 2025 Ultra Librarian. All rights reserved.
Wurth_Power Magnetics_WE-XHMI: Copyright: Würth Elektronik
